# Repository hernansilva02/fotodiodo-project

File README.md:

# Fotodiodo Project — Detector con fotodiodo + TIA

Proyecto académico/open-hardware para el diseño, simulación y fabricación de un detector basado en **fotodiodo PIN** con **amplificador transimpedancia (TIA)**. El repositorio incluye esquemáticos y PCB en KiCad, modelos/SPICE para simulación, gerbers listos para fabricación y documentación en LaTeX.

> Licencia: **CERN Open Hardware License v1.2** (incluida en el repo).

---

## ✨ Características

- **Hardware KiCad**: esquemáticos y PCB en `KiCAD/` con vistas 2D/3D y archivos de fabricación en `gerbers/`.
- **Simulación**: netlists y archivos en `spice/` para análisis de ruido, frecuencia y transitorios del TIA.
- **Documentación**: fuentes LaTeX en `docs/` (compilables con `latexmk` o `pdflatex + bibtex`).
- **Datasheets** de componentes relevantes en `datasheets/`.
- **Licencia**: archivo `CERN_OPEN_HARDWARE_LICENSE_OHL_v_1_2.txt` en la raíz.

---

## 🔧 Requisitos

- **KiCad** (>= 6.x recomendado) para abrir `KiCAD/`.
- **Simulador SPICE** (LTspice/Ngspice) para `spice/`.
- **LaTeX** para compilar `docs/` (p. ej. `latexmk` o `pdflatex + bibtex`).

---

## ▶️ Cómo usar

### 1) Hardware (KiCad)
1. Abrí el proyecto desde `KiCAD/`.
2. Revisá el esquemático y el stackup; validá DRC/ERC.
3. Para visualizar en 3D, usá el visor de KiCad.
4. Si necesitás fabricar, exportá desde el proyecto o usá los **archivos listos** en `gerbers/`.

### 2) Simulación (SPICE)
1. Abrí los archivos de `spice/` con tu simulador.
2. Corré análisis **AC** (ganancia/banda), **TRAN** (respuesta a pulsos) y **ruido**.
3. Ajustá la **Rf** del TIA y **Cf** de compensación según tu fotodiodo/carga esperada.

### 3) Documentación (LaTeX)
- Compilación rápida:
  ```bash
  cd docs
  latexmk -pdf
  # o, alternativamente
  pdflatex main.tex && bibtex main && pdflatex main.tex && pdflatex main.tex

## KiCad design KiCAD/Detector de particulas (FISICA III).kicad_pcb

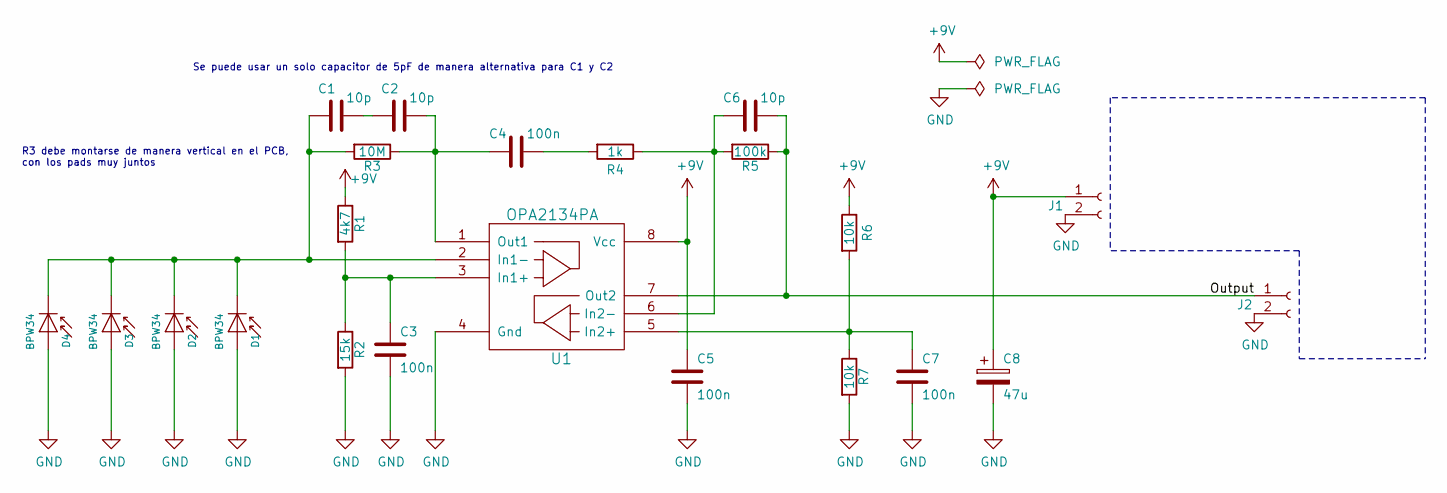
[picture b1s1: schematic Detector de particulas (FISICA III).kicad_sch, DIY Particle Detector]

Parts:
C1, C2: 10p; C_Disc_D3.0mm_W1.6mm_P2.50mm; MFG_PN MC0805N100J101A2.54MM; FARNELL 1694175
C3, C5, C7: 100n; C_Disc_D3.0mm_W1.6mm_P2.50mm; MFG_PN MC0805Y104M500A2.54MM; FARNELL 2112751
C4: 100n; C_Disc_D3.0mm_W1.6mm_P2.50mm; MFG_PN C320C474M5U5TA; FARNELL 1457660
C6: 10p; C_Disc_D3.0mm_W1.6mm_P2.50mm; MFG_PN TS170R1H332KSBBA0R; FARNELL 2901293
C8: 47u; CP_Radial_D6.3mm_P2.50mm; MFG_PN ECA-1JHG470; FARNELL 9693033
D1, D2, D3: BPW34; Osram_BPW34S-SMD; MFG_PN BPW34F/FA; FARNELL 2981621
D4: BPW34; Osram_BPW34S-SMD; MFG_PN BPX61; FARNELL 2981630
J1, J2: Conn_01x02_Female; PinHeader_1x02_P2.54mm_Vertical
R1: 4k7; R_Axial_DIN0207_L6.3mm_D2.5mm_P7.62mm_Horizontal; MFG_PN MCMF006FF4701A50; FARNELL 2401772
R2: 15k; R_Axial_DIN0207_L6.3mm_D2.5mm_P7.62mm_Horizontal; MFG_PN MCMF006FF1502A50; FARNELL 2401785
R3: 10M; R_Axial_DIN0204_L3.6mm_D1.6mm_P7.62mm_Horizontal; MFG_PN RH73H2A40MKTN; FARNELL 1174521
R4: 1k; R_Axial_DIN0207_L6.3mm_D2.5mm_P7.62mm_Horizontal; MFG_PN MCMF006FF4701A50; FARNELL 2401772
R5: 100k; R_Axial_DIN0207_L6.3mm_D2.5mm_P7.62mm_Horizontal; MFG_PN MCMF006FF1004A50; FARNELL 2401807
R6, R7: 10k; R_Axial_DIN0207_L6.3mm_D2.5mm_P7.62mm_Horizontal; MFG_PN MCMF006FF1002A50; FARNELL 2401780
U1: OPA2134PA; DIP-8_W7.62mm; FARNELL 3117956

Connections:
+9V: C5.1, C8.1, J1.1, R1.1, R6.1, U1.8 (Vcc)
/Output: C6.2, J2.1, R5.1, U1.7 (Out2)
GND: C3.2, C5.2, C7.2, C8.2, D1.2 (A), D2.2 (A), D3.2 (A), D4.2 (A), J1.2, J2.2, R2.2, R7.2, U1.4 (Gnd)
unnamed: C1.2, C2.1
unnamed: C4.2, R4.2
unnamed: C1.1, D1.1 (K), D2.1 (K), D3.1 (K), D4.1 (K), R3.2, U1.2 (In1-)
unnamed: C3.1, R1.2, R2.1, U1.3 (In1+)
unnamed: C7.1, R6.2, R7.1, U1.5 (In2+)
unnamed: C6.1, R4.1, R5.2, U1.6 (In2-)
unnamed: C2.2, C4.1, R3.1, U1.1 (Out1)

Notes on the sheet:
Se puede usar un solo capacitor de 5pF de manera alternativa para C1 y C2
R3 debe montarse de manera vertical en el PCB, con los pads muy juntos

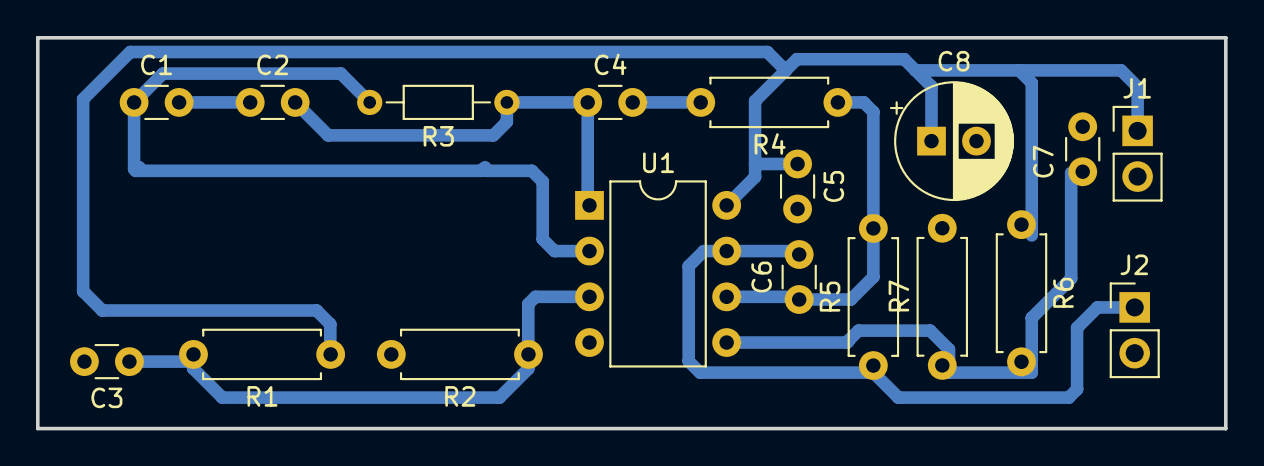
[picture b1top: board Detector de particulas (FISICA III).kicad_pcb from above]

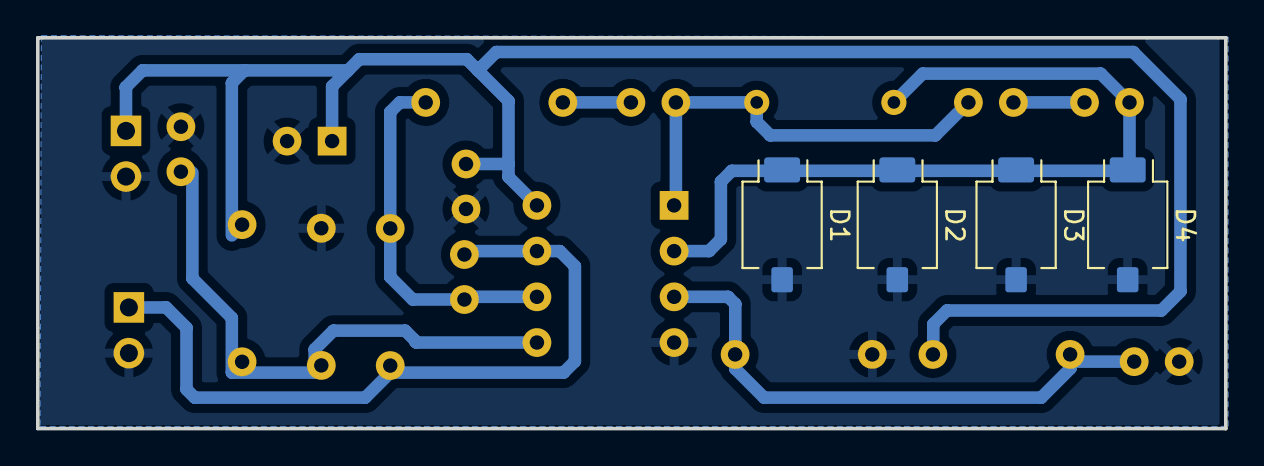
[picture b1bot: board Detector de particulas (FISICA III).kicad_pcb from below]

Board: 2 copper layers, 66.0 x 21.7 mm, 22 parts (4 on the bottom side), 10 nets.

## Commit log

2025-10-01 first
2025-10-03 formato IEEE empezado
2025-10-07 ya esta el template de referencias. Avances
2025-10-08 ppio de funcionamiento avanzado
2025-10-08 repo actualizado
2025-10-08 readme
2025-10-08 readme again
2025-10-14 bastante documentacion y algunos testeos
2025-10-15 un poco de limpieza del repo
2025-10-16 nuevo pcb
2025-10-16 nuevo pcb completo
2025-10-17 imagenes, etc
2025-10-18 sim + order del repo
2025-10-19 tercera seccion del informe
2025-10-20 etapa de deteccion completa
2025-10-20 primera version terminada
2025-10-20 informe v2
2025-10-20 readme actualizado
2025-10-20 readme corregido
2025-10-23 circuito en circuitikz terminado
2025-10-23 corrección primer entrega
2025-10-24 nueva simulacion
